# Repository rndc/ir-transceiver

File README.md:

# ir-transceiver

Infrared Transceiver using ATmega328P.

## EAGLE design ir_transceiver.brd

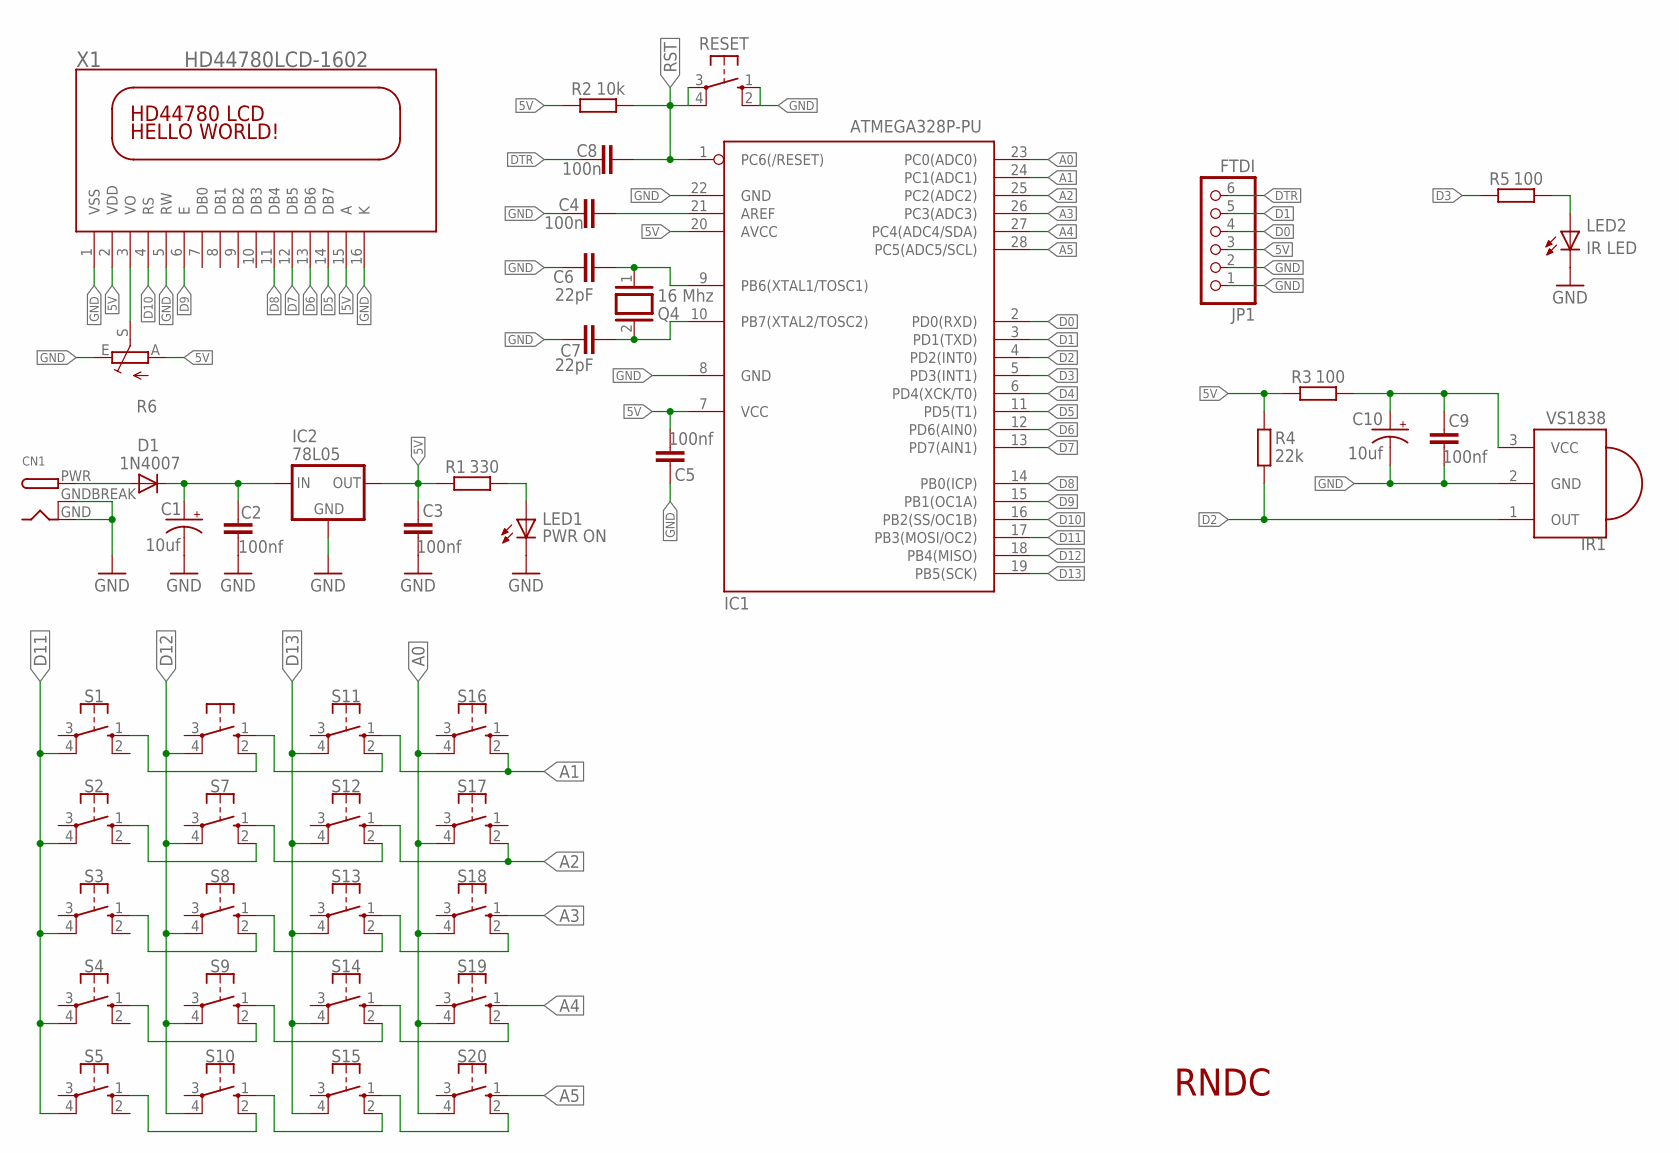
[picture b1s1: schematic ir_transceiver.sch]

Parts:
C1, C10: 10uf; TT2D4
C2, C3, C5, C9: 100nf; C025-024X044
C4, C8: 100n; C025-024X044
C6, C7: 22pF; C025-024X044
CN1: DCBARRELPTH; DCJACK_2MM_PTH
D1: 1N4007; DO35-7
IC1: ATMEGA328P-PU; DIL28-3
IC2: 78L05; 78LXX
IR1: VS1838
JP1: FTDI; 1X06
LED1: PWR ON; LED3MM
LED2: IR LED; LED5MM
Q4: 16 Mhz; QS
R1: 330; 0207_10
R2: 10k; 0207_10
R3, R5: 100; 0207_10
R4: 22k; 0207_10
R6: TRIM_EU-CA6V; CA6V
RESET: 10-XX; B3F-10XX
S1, S2, S3, S4, S5, S6, S7, S8, S9, S10, S11, S12, S13, S14, S15, S16, S17, S18, S19, S20: 10-XX; B3F-10XX
X1: HD44780LCD-1602; LCD1602

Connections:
5V: C3.2, C5.2, IC1.7 (VCC), IC1.20 (AVCC), IC2.OUT, JP1.3, R1.2, R2.2, R3.2, R4.1, R6.A, X1.2 (VDD), X1.15 (A)
A0: IC1.23 (PC0(ADC0)), S16.4 (P1), S17.4 (P1), S18.4 (P1), S19.4 (P1), S20.4 (P1)
A1: IC1.24 (PC1(ADC1)), S11.1 (S), S16.2 (S1)
A2: IC1.25 (PC2(ADC2)), S12.1 (S), S17.2 (S1)
A3: IC1.26 (PC3(ADC3)), S18.1 (S)
A4: IC1.27 (PC4(ADC4/SDA)), S19.1 (S)
A5: IC1.28 (PC5(ADC5/SCL)), S20.1 (S)
D0: IC1.2 (PD0(RXD)), JP1.4
D1: IC1.3 (PD1(TXD)), JP1.5
D2: IC1.4 (PD2(INT0)), IR1.1 (OUT), R4.2
D3: IC1.5 (PD3(INT1)), R5.2
D4: IC1.6 (PD4(XCK/T0))
D5: IC1.11 (PD5(T1)), X1.14 (DB7)
D6: IC1.12 (PD6(AIN0)), X1.13 (DB6)
D7: IC1.13 (PD7(AIN1)), X1.12 (DB5)
D8: IC1.14 (PB0(ICP)), X1.11 (DB4)
D9: IC1.15 (PB1(OC1A)), X1.6 (E)
D10: IC1.16 (PB2(SS/OC1B)), X1.4 (RS)
D11: IC1.17 (PB3(MOSI/OC2)), S1.4 (P1), S2.4 (P1), S3.4 (P1), S4.4 (P1), S5.4 (P1)
D12: IC1.18 (PB4(MISO)), S6.4 (P1), S7.4 (P1), S8.4 (P1), S9.4 (P1), S10.4 (P1)
D13: IC1.19 (PB5(SCK)), S11.4 (P1), S12.4 (P1), S13.4 (P1), S14.4 (P1), S15.4 (P1)
DTR: C8.1, JP1.6
GND: C1.-, C2.1, C3.1, C4.1, C5.1, C6.2, C7.2, C9.1, C10.-, CN1.GND, CN1.GNDBREAK, IC1.8 (GND), IC1.22 (GND), IC2.GND, IR1.2 (GND), JP1.1, JP1.2, LED1.K (C), LED2.K (C), R6.E, RESET.1 (S), RESET.2 (S1), X1.1 (VSS), X1.5 (RW), X1.16 (K)
unnamed: C9.2, C10.+, IR1.3 (VCC), R3.1
unnamed: LED1.A, R1.1
unnamed: C4.2, IC1.21 (AREF)
unnamed: LED2.A, R5.1
unnamed: R6.S, X1.3 (VO)
unnamed: S13.1 (S), S18.2 (S1)
unnamed: S1.1 (S), S6.2 (S1)
unnamed: S2.1 (S), S7.2 (S1)
unnamed: S3.1 (S), S8.2 (S1)
unnamed: S4.1 (S), S9.2 (S1)
unnamed: S5.1 (S), S10.2 (S1)
unnamed: C6.1, IC1.9 (PB6(XTAL1/TOSC1)), Q4.1
unnamed: C7.1, IC1.10 (PB7(XTAL2/TOSC2)), Q4.2
unnamed: CN1.PWR, D1.A
unnamed: S6.1 (S), S11.2 (S1)
unnamed: S7.1 (S), S12.2 (S1)
unnamed: S8.1 (S), S13.2 (S1)
unnamed: S9.1 (S), S14.2 (S1)
unnamed: S10.1 (S), S15.2 (S1)
unnamed: S14.1 (S), S19.2 (S1)
unnamed: S15.1 (S), S20.2 (S1)
RST: C8.2, IC1.1 (PC6(/RESET)), R2.1, RESET.3, RESET.4 (P1)
VIN: C1.+, C2.2, D1.C, IC2.IN

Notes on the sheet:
RNDC

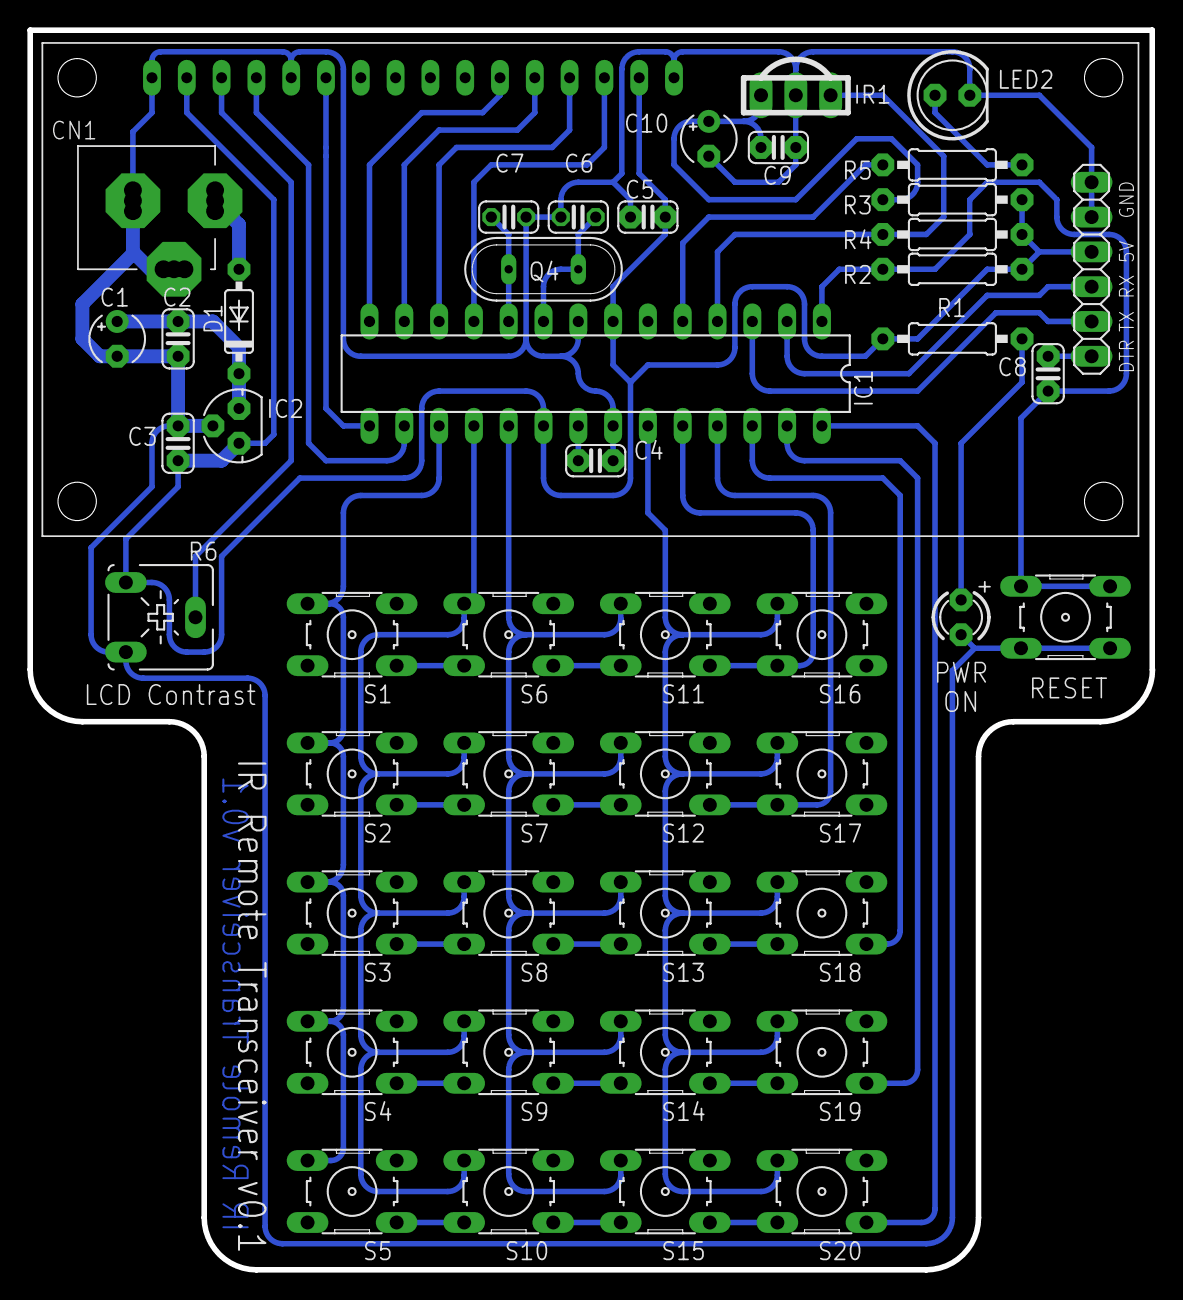
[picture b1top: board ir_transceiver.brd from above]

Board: 2 copper layers, 81.9 x 90.5 mm, 47 parts (0 on the bottom side), 45 nets.

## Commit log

2016-01-08 Initial commit :sparkles:
2016-01-08 Fix board layout image
